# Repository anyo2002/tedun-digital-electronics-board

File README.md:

# TEDUN - Digital Electronics Development Board

## 📌 Overview
The **TEDUN (Tarjeta de Electrónica Digital de la UNAL)** is an academic project developed as part of an Embedded Systems course in Electronic Engineering.

> ⚠️ Note: The project name does not represent an official product of UNAL. It only reflects the academic context in which it was developed.

This project consists of the design and implementation of a **custom development board** based on:
- A **F133A RISC-V processor**
- A **Trion T8Q144C3 FPGA**

The board enables hardware experimentation with multiple modules (Bluetooth, audio, infrared, etc.) using communication protocols such as **UART, I2S, SPI**, and **GPIO**.

---

## 🎯 Objectives
- Design a complete embedded development board
- Enable communication between a processor and an FPGA
- Support hardware testing using multiple digital interfaces
- Develop schematics and PCB using KiCad
- Implement FPGA programming using open-source tools

---

## ⚙️ Key Features

- Powered via **Micro-USB (~5V)**
- Boot via **SD card with Tina Linux**
- UART communication with a computer (via USB-UART converter)
- FPGA programming using **OpenOCD (JTAG)**
- Communication between F133A and FPGA via **UART or SPI**
- 32 GPIO pins organized in **4 banks (3.3V + 5V output)**

---

## 🏗️ System Architecture

The system integrates:
- F133A processor (RISC-V)
- Trion T8 FPGA
- SD card storage
- Multiple communication interfaces

### Interfaces

#### 🔹 JTAG
Used to program the FPGA through OpenOCD running on the F133A.

#### 🔹 SD Card
Stores:
- Tina Linux OS
- Boot partitions
- Drivers and applications
- FPGA configuration files

#### 🔹 UART & I2S
- UART for communication with PC and FPGA
- I2S for audio/data transmission

#### 🔹 GPIO
- 32 configurable pins
- Used for hardware testing and module integration

---

## 🧩 Block Diagram

---

## 🔌 Interface Design

To validate the system, an **LctechPi board (F133A-based)** was used for testing.

Key points:
- Tina Linux was configured and deployed
- Required system packages were installed
- WiFi was tested but not included (cost optimization)

### Tool Selection

Two tools were evaluated:

#### ❌ openFPGALoader
- Supports Trion FPGA
- Limited to memory-based programming (Flash)
- ❌ Not suitable for JTAG-based programming via F133A

#### ✅ OpenOCD
- Open-source
- Supports JTAG
- Compatible with Trion FPGA
- ✔️ Selected solution

---

## 🧪 FPGA Programming with OpenOCD

OpenOCD was compiled for RISC-V and deployed on the board.

### Setup Steps:
1. Compile OpenOCD from source:
   https://github.com/riscv/riscv-openocd

2. Copy binary to:
/bin/

3. Copy scripts to:
/usr/local/share/openocd/scripts

4. Create configuration file:
openocd.cfg

### Example Configuration (JTAG via GPIO)

```bash
adapter driver sysfsgpio
transport select jtag
sysfsgpio jtag_nums 2 3 1 4

set CHIPNAME fpga_trion
source [find fpga/efinix_trion.cfg]

init
pld load fpga_trion.pld GPIO_demo.bit
```

## 🛠️ Hardware Design

The hardware design is based on:

- MangoPi (F133A reference)

- LctechPi board

- Trion T8 FPGA reference boards

## 🔋 Power Supply

- Input: Micro-USB (5V)
- Regulation using:
  - AMS1117 (instead of RY1303 from the MangoPi board)
  - Multiple LDO regulators

## Voltage Levels:
- 3.3V → I/O, GPIO, oscillator

- 1.8V → DRAM

- 2.8V → Communication block (PE)

- 1.2V → FPGA core

- 0.9V → Processor core

## ⚡ Power Sequencing

Implemented using:
- LM3880 power sequencer

Sequence: 
1. Enable FPGA + DRAM + PE
2. Enable processor core (0.9V)
3. Enable FPGA I/O

## 💾 SD Card
- Used for booting Tina Linux
- Based on MangoPi reference design

- Direct connection to F133A

## 🧠 F133A Connections

- JTAG → PG6–PG9
- UART0 → PE2 / PE3
- UART → PC6 / PC7
- SD → PF0–PF6
- SPI → PC2–PC7

## 🔲 FPGA (Trion T8)

- 13 banks available
- Selected banks: 1A, 3A, 3BC, 3D
- Supports:
  - JTAG programming
  - SPI & UART communication
  - GPIO expansion

## 🔌 GPIO

- 32 GPIO pins (4 banks × 8 pins)
- Each bank includes:
  - 3.3V output
  - GND
- Additional:
  - 5V output
  - UART interface
## ⏱️ Oscillators
- FPGA: 25 MHz oscillator

- Processor: MangoPi reference oscillator

## 🧾 PCB Design

Designed in KiCad:
- Compact layout
- Optimized routing
- 3D visualization available

## 📍 Pinout

- 32 GPIO pins available
- Organized in 4 banks
- Flexible usage:
  - GPIO
  - Communication interfaces
  - Special FPGA functions

## 📚 References
- F133A Datasheet
- Trion T8 Datasheet
- MangoPi Schematics

## 🧰 Tools & Technologies
- KiCad (PCB design)
- OpenOCD (FPGA programming)
- Tina Linux
- RISC-V architecture
- Embedded Linux

## 🚀 Skills Demonstrated
- Embedded Systems Design
- FPGA Integration
- Hardware Architecture
- PCB Design (KiCad)
- Power Electronics (LDO, sequencing)
- Communication Protocols (UART, SPI, I2S, JTAG)

## 👤 Authors

- Angel RUIZ
- Santiago DIAZ
- Daniel CELY

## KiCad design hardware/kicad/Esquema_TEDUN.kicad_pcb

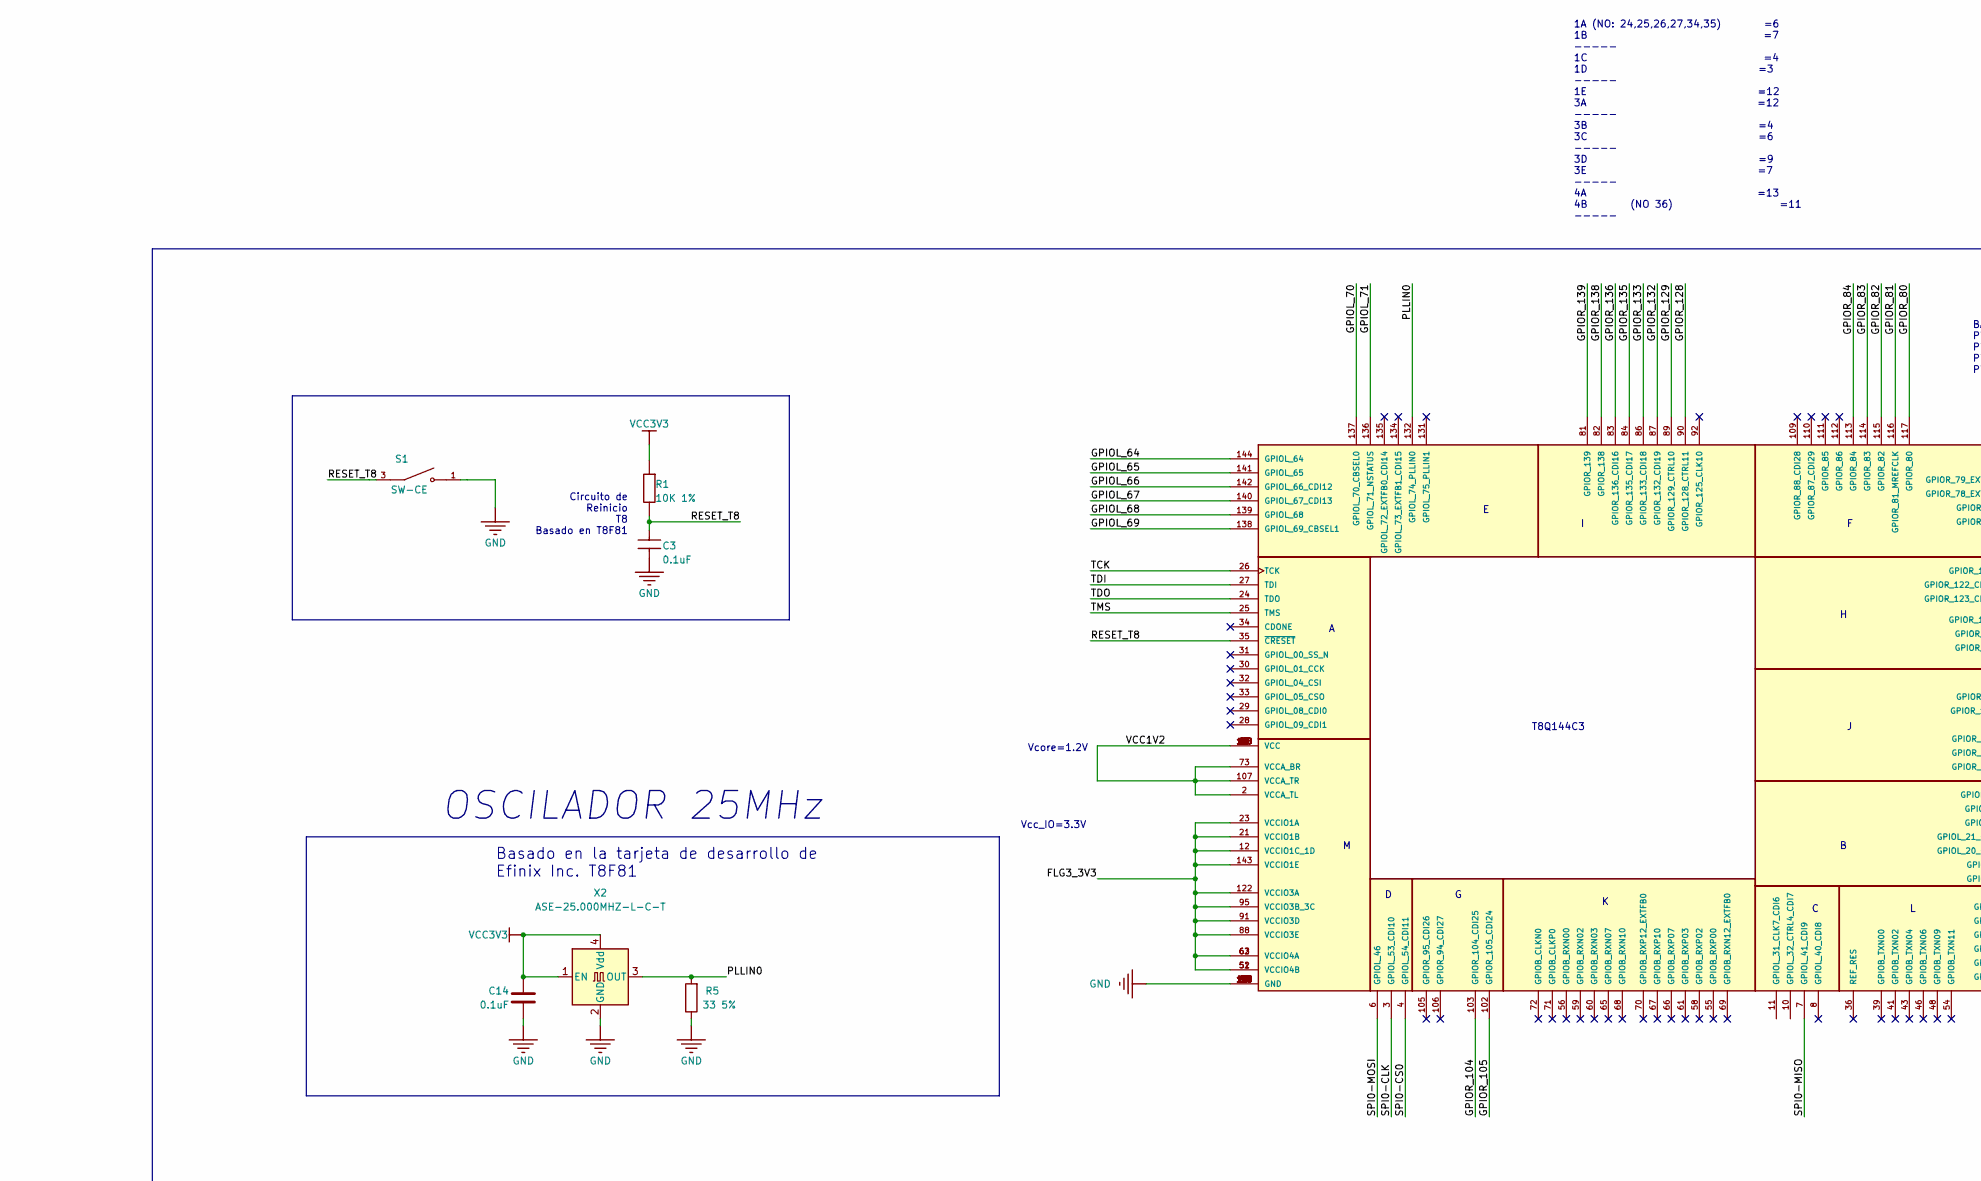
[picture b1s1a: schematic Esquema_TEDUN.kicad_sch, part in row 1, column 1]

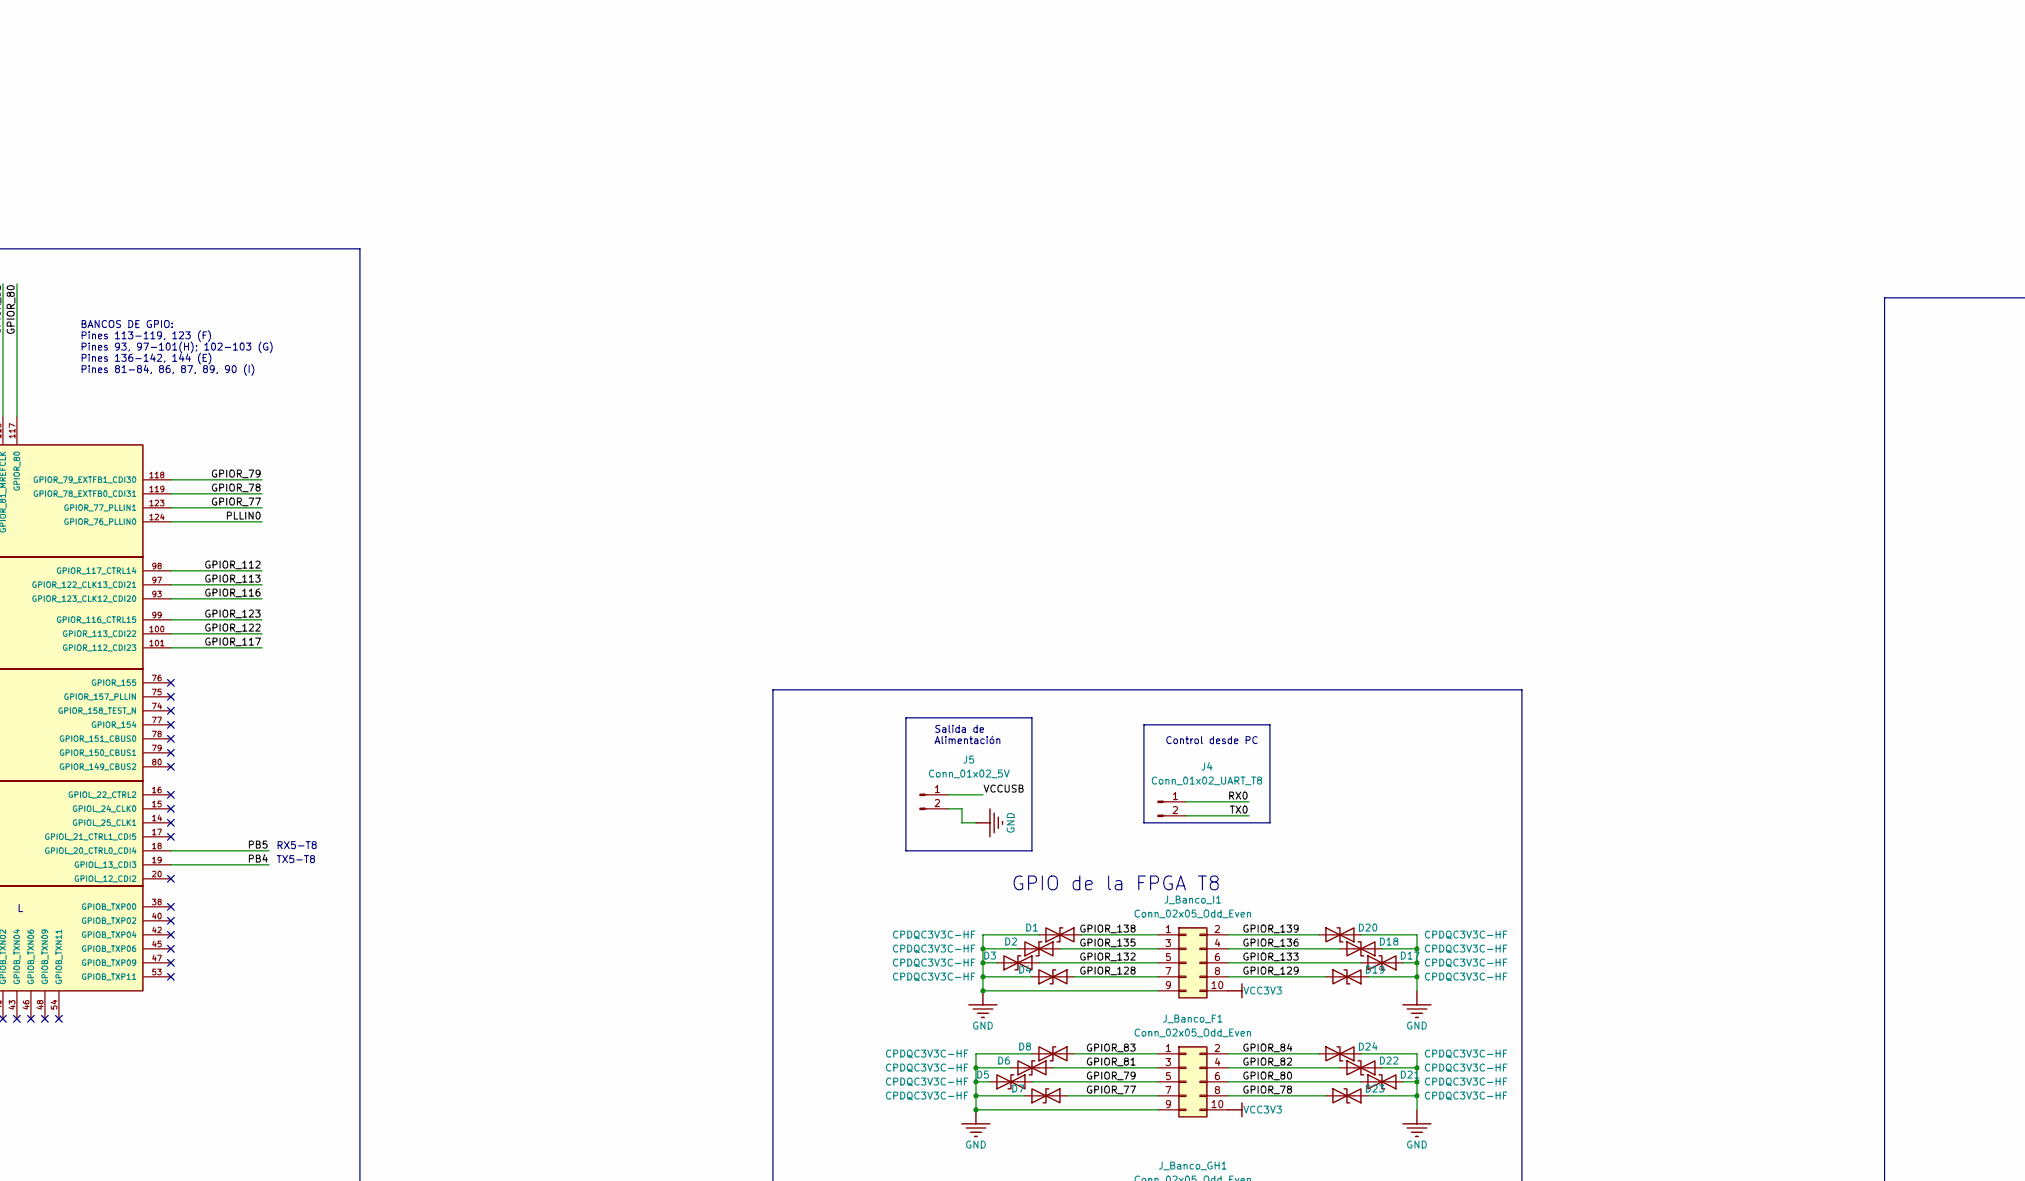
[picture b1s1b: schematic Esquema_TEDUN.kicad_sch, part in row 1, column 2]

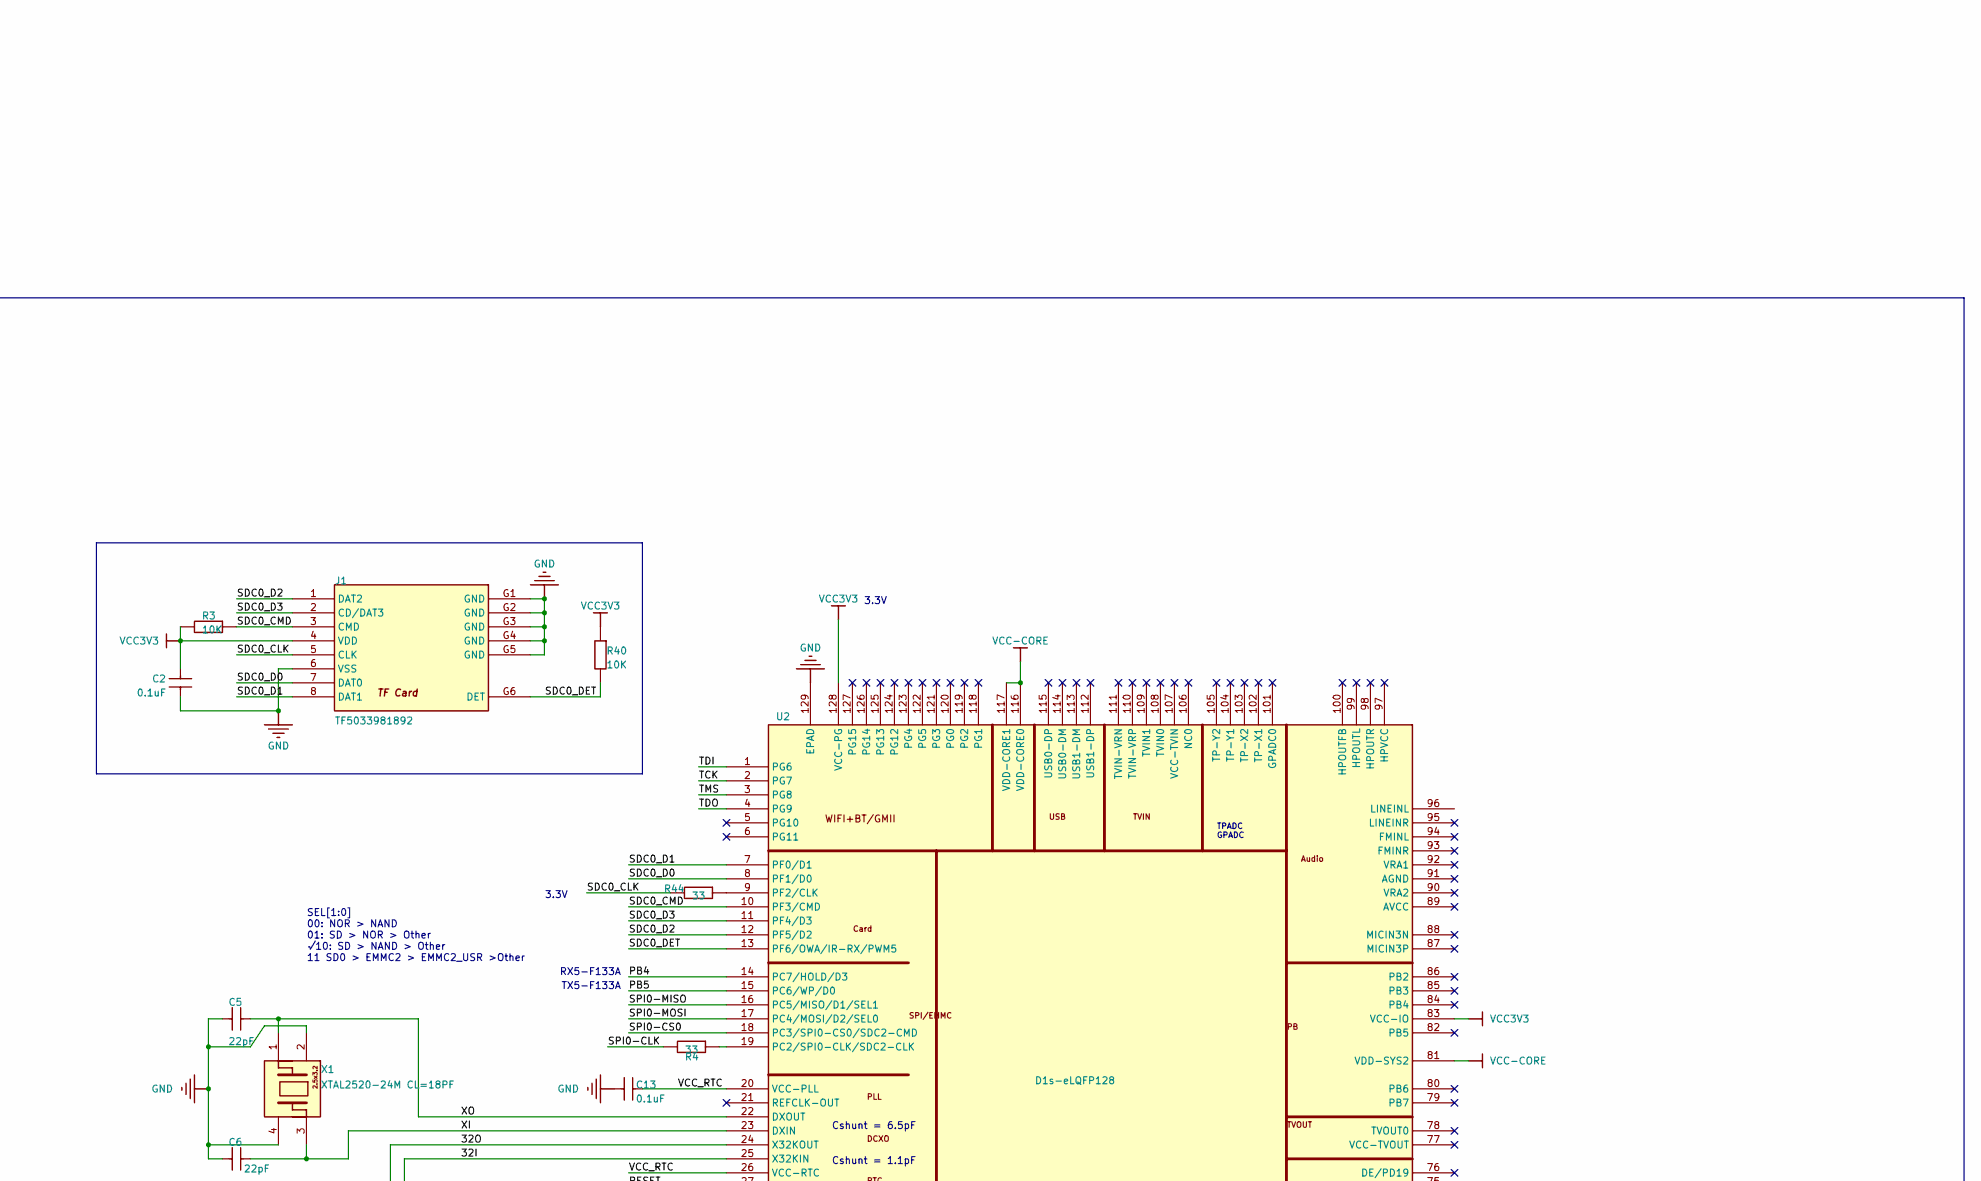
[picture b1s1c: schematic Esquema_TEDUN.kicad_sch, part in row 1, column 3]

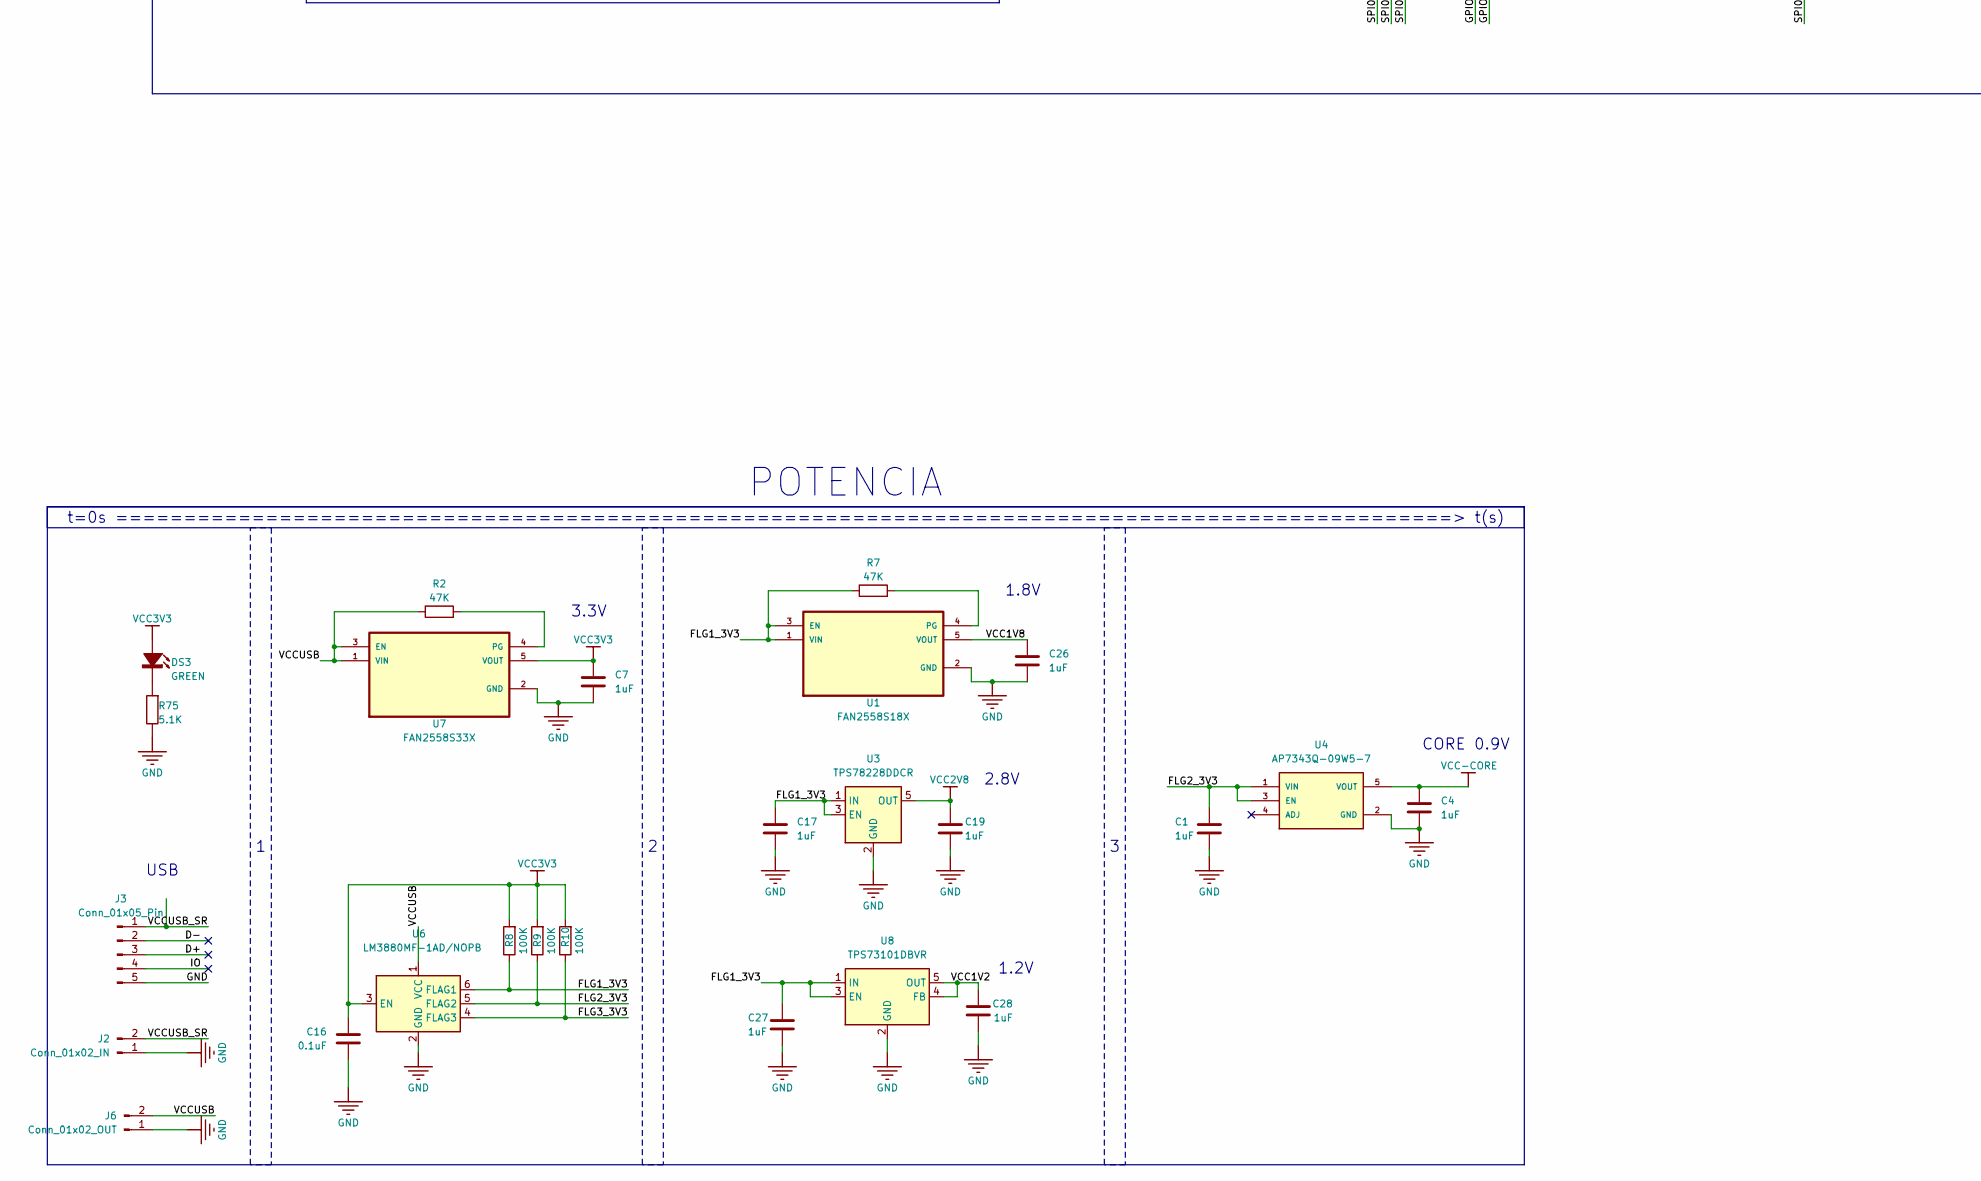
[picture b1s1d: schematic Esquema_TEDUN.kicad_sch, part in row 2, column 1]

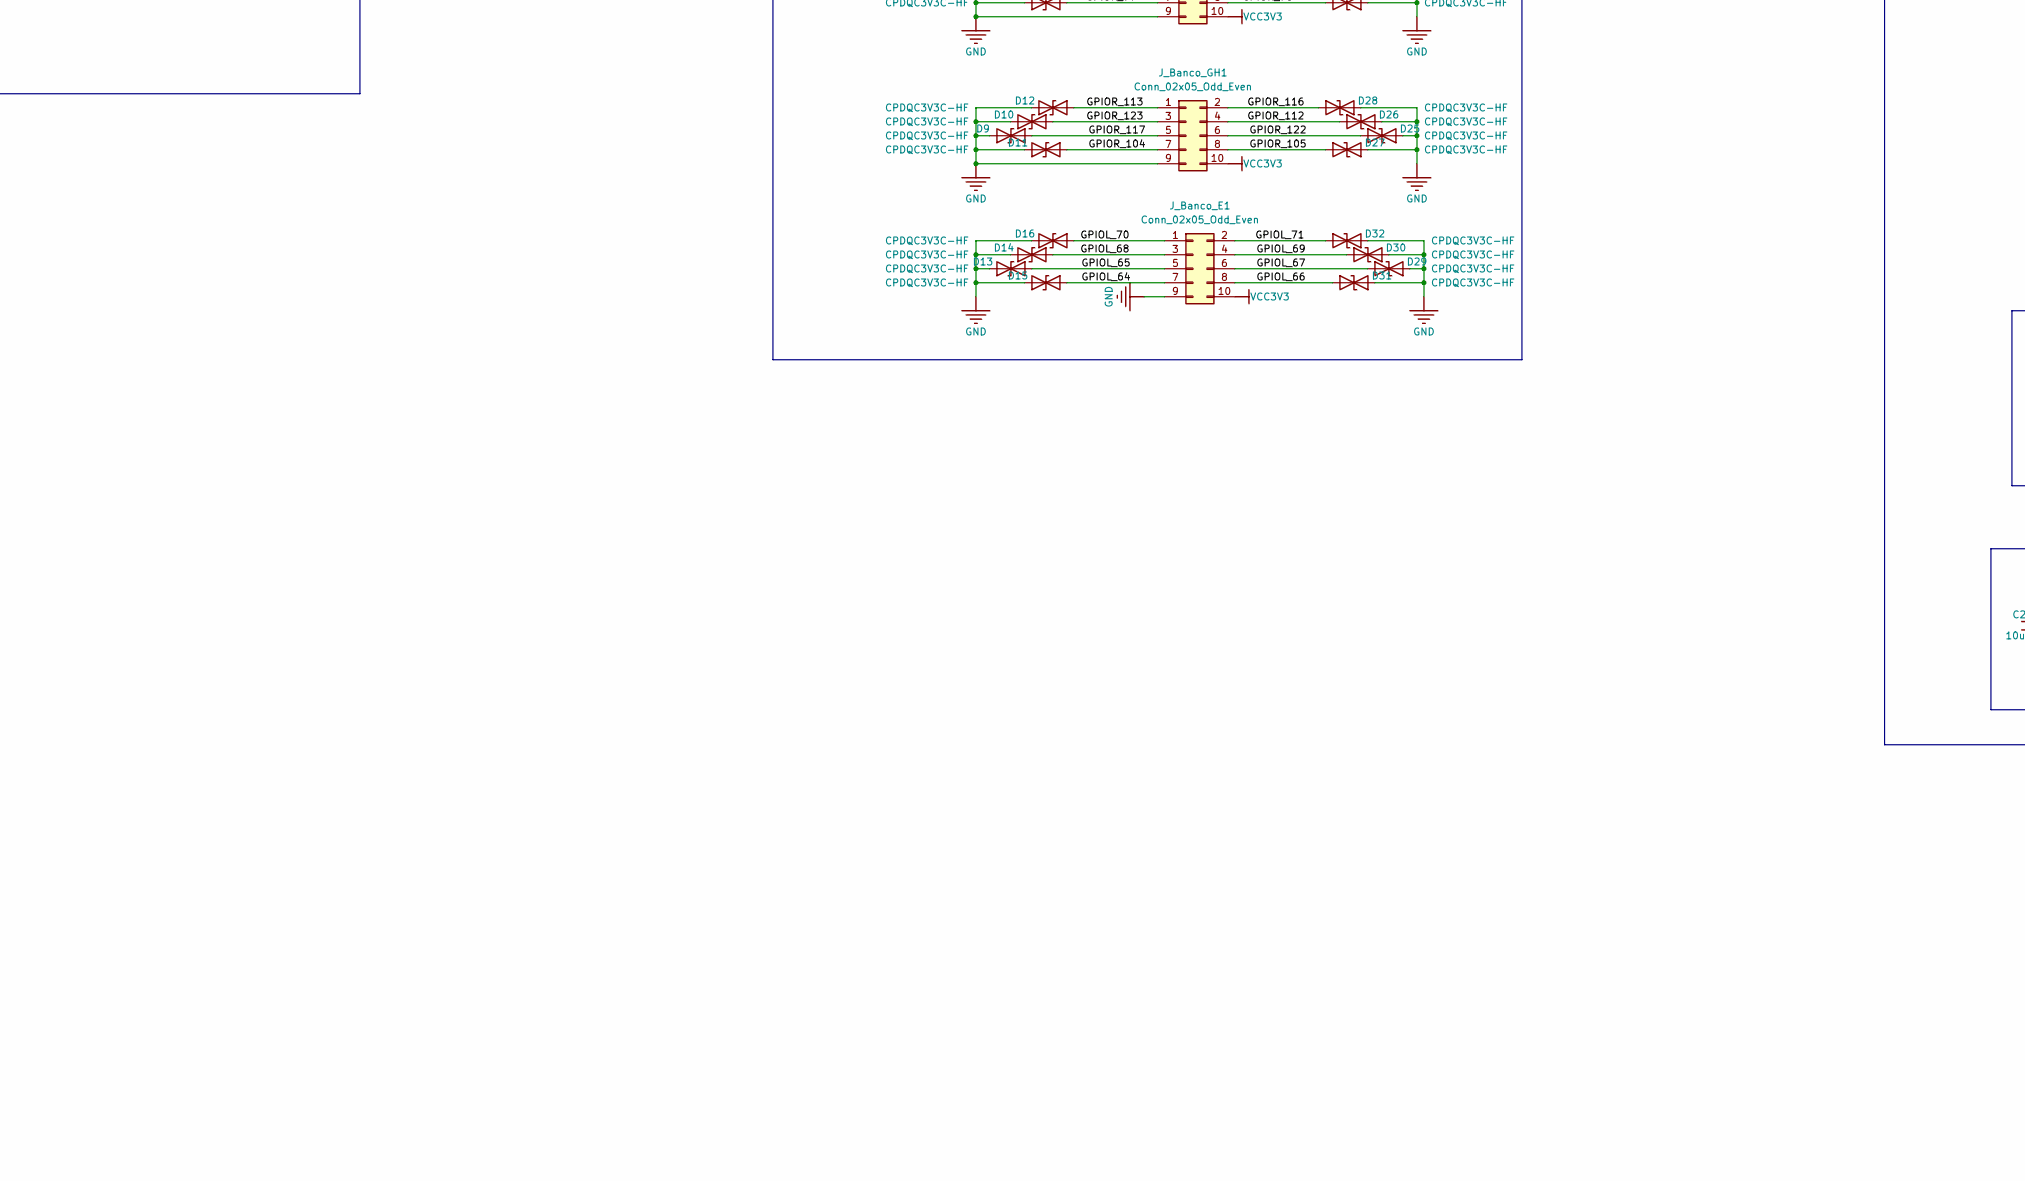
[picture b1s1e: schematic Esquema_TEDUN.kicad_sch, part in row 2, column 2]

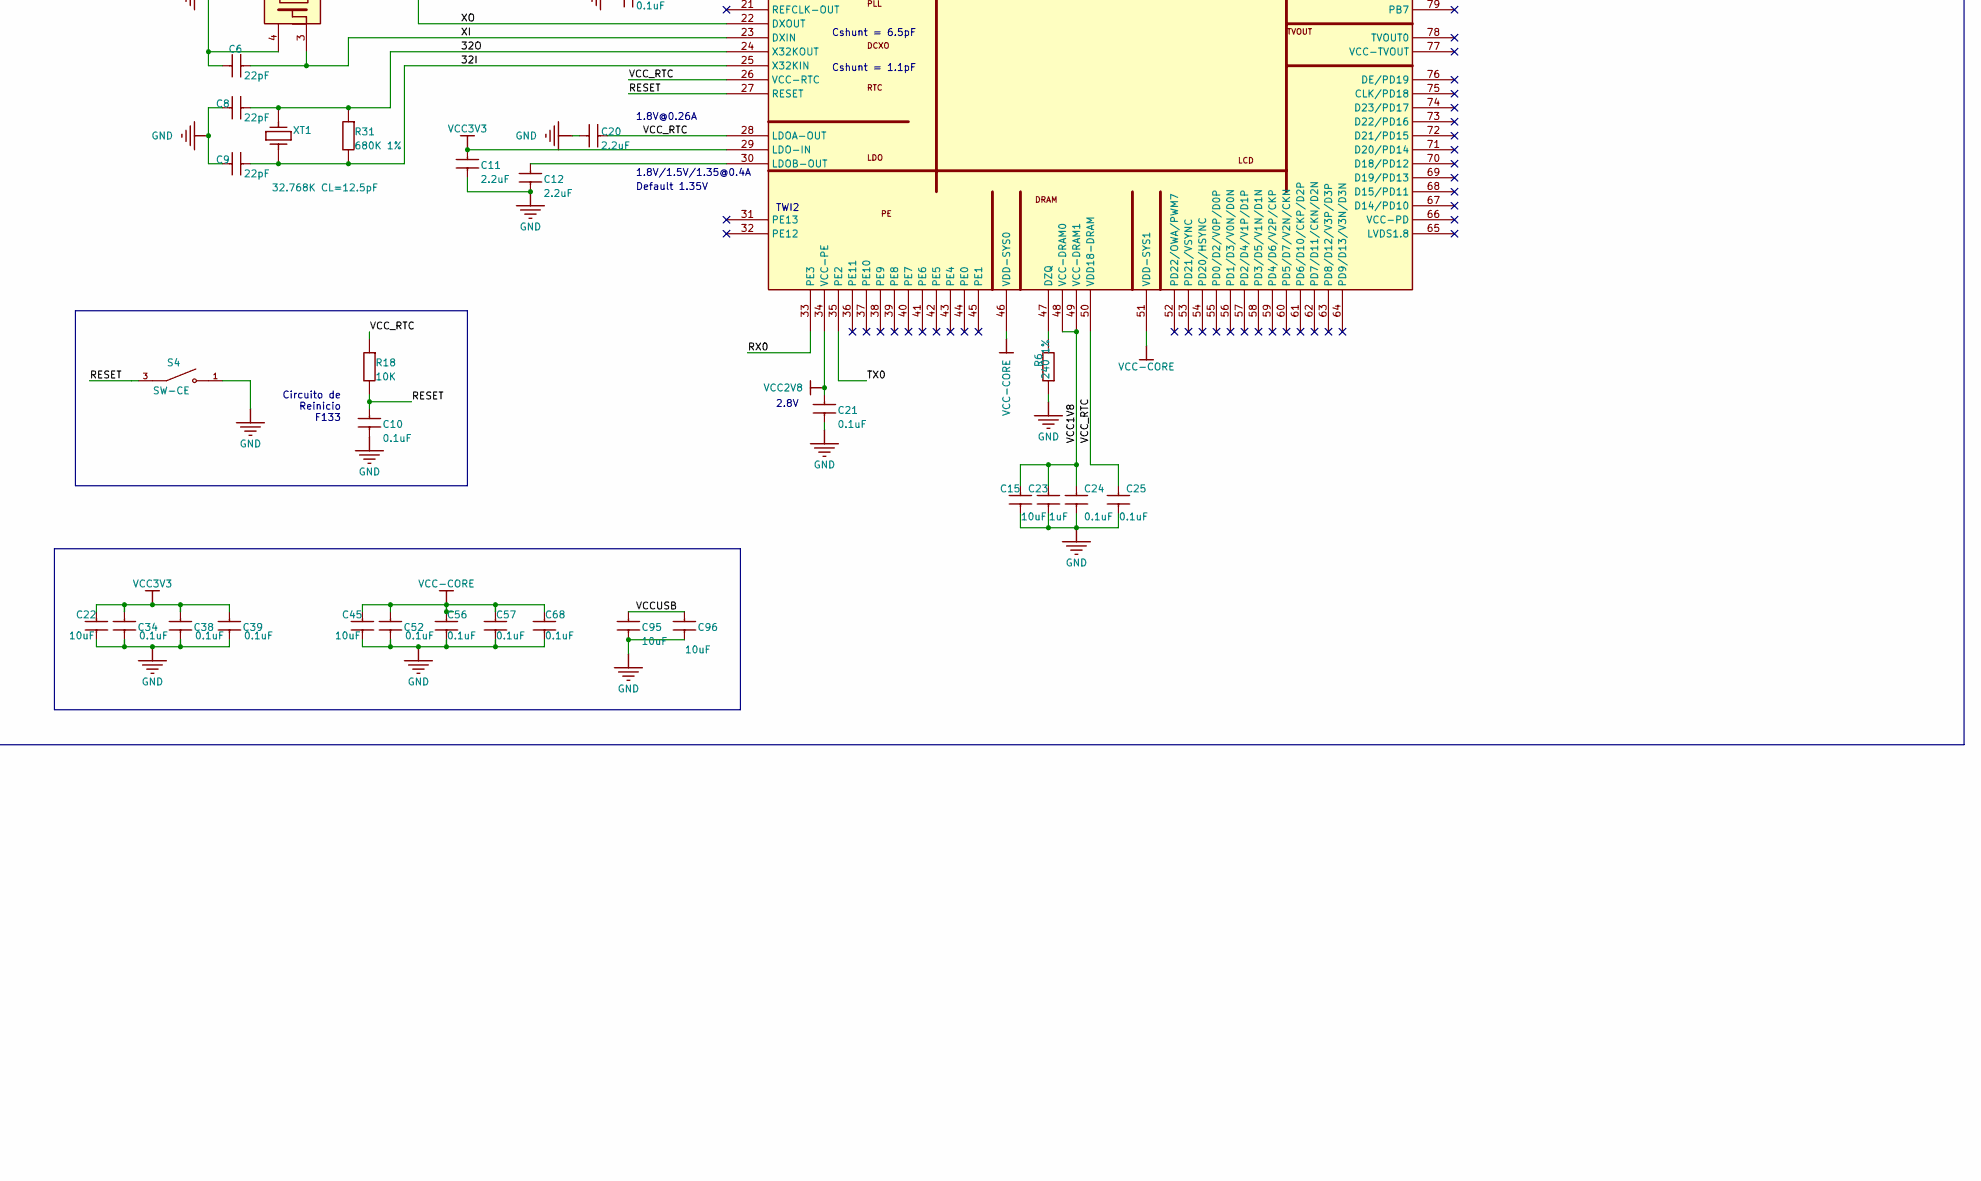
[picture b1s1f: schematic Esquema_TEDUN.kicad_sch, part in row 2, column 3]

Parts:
C1, C4, C7, C17, C19, C23, C26, C27, C28: 1uF; C_0402_1005Metric_Pad0.74x0.62mm_HandSolder
C2, C3, C10, C13, C14, C16, C21, C24, C25, C34, C38, C39, C52, C56, C57, C68: 0.1uF; C_0402_1005Metric_Pad0.74x0.62mm_HandSolder
C5, C6, C8, C9: 22pF; C_0402_1005Metric_Pad0.74x0.62mm_HandSolder
C11, C12, C20: 2.2uF; C_0402_1005Metric_Pad0.74x0.62mm_HandSolder
C15, C22, C45, C95, C96: 10uF; C_0402_1005Metric_Pad0.74x0.62mm_HandSolder
D1, D2, D3, D4, D5, D6, D7, D8, D9, D10, D11, D12, D13, D14, D15, D16, D17, D18, D19, D20, D21, D22, D23, D24, D25, D26, D27, D28, D29, D30, D31, D32: CPDQC3V3C-HF; DIODFN100X60X43-2N
DS3: GREEN; LED_0402_1005Metric_Pad0.77x0.64mm_HandSolder
J1: TF5033981892; TFCARD-1040310811
J2: Conn_01x02_IN; PinHeader_1x02_P2.54mm_Vertical
J3: Conn_01x05_Pin; PinHeader_1x05_P2.54mm_Vertical
J4: Conn_01x02_UART_T8; PinHeader_1x02_P2.54mm_Vertical
J5: Conn_01x02_5V; PinHeader_1x02_P2.54mm_Vertical
J6: Conn_01x02_OUT; PinHeader_1x02_P2.54mm_Vertical
J_Banco_E1: Conn_02x05_Odd_Even; PinHeader_2x05_P2.54mm_Vertical
J_Banco_F1: Conn_02x05_Odd_Even; PinHeader_2x05_P2.54mm_Vertical
J_Banco_GH1: Conn_02x05_Odd_Even; PinHeader_2x05_P2.54mm_Vertical
J_Banco_I1: Conn_02x05_Odd_Even; PinHeader_2x05_P2.54mm_Vertical
R1: 10K 1%; R_0402_1005Metric_Pad0.72x0.64mm_HandSolder
R2, R7: 47K; R_0402_1005Metric_Pad0.72x0.64mm_HandSolder
R3, R18, R40: 10K; R_0402_1005Metric_Pad0.72x0.64mm_HandSolder
R4, R44: 33; R_0402_1005Metric_Pad0.72x0.64mm_HandSolder
R5: 33 5%; R_0402_1005Metric_Pad0.72x0.64mm_HandSolder
R6: 240 1%; R_0402_1005Metric_Pad0.72x0.64mm_HandSolder
R8, R9, R10: 100K; R_0402_1005Metric_Pad0.72x0.64mm_HandSolder
R31: 680K 1%; R_0402_1005Metric_Pad0.72x0.64mm_HandSolder
R75: 5.1K; R_0402_1005Metric_Pad0.72x0.64mm_HandSolder
S1, S4: SW-CE; SW_PTS_647_SM38_SMTR2_LFS; PARTREV 11 Jun 19; DigiKey_Part_Number PTS647SM38SMTR2LFSTR-ND
U1: FAN2558S18X; FAN2558S33X
U2: D1s-eLQFP128; F133A_QFP129
U3: TPS78228DDCR; SOT-23-5
U4: AP7343Q-09W5-7; SOT-23-5
U5: T8Q144C3; QFP50P2200X2200X160-144N; PARTREV V3.6
U6: LM3880MF-1AD/NOPB; SOT-23-6
U7: FAN2558S33X
U8: TPS73101DBVR; SOT-23-5
X1: XTAL2520-24M CL=18PF; Oscillator_SMD_ECS_2520MV-xxx-xx-4Pin_2.5x2.0mm
X2: ASE-25.000MHZ-L-C-T; Oscillator_SMD_Abracon_ASE-4Pin_3.2x2.5mm
XT1: 32.768K CL=12.5pF; Y3215

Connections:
/32I: C9.1, R31.2, U2.25 (X32KIN), XT1.1
/32O: C8.1, R31.1, U2.24 (X32KOUT), XT1.2
/D+: J3.3
/D-: J3.2
/FLG1_3V3: C17.2, C27.1, R7.1, R8.1, U1.1 (VIN), U1.3 (EN), U3.1 (IN), U3.3 (EN), U6.6 (FLAG1), U8.1 (IN), U8.3 (EN)
/FLG2_3V3: C1.1, R9.1, U4.1 (VIN), U4.3 (EN), U6.5 (FLAG2)
/FLG3_3V3: R10.1, U5.12 (VCCIO1C_1D), U5.21 (VCCIO1B), U5.23 (VCCIO1A), U5.51 (VCCIO4B), U5.52 (VCCIO4B), U5.62 (VCCIO4A), U5.63 (VCCIO4A), U5.88 (VCCIO3E), U5.91 (VCCIO3D), U5.95 (VCCIO3B_3C), U5.122 (VCCIO3A), U5.143 (VCCIO1E), U6.4 (FLAG3)
/GPIOL_64: D15.2 (A2), J_Banco_E1.7, U5.144 (GPIOL_64)
/GPIOL_65: D13.2 (A2), J_Banco_E1.5, U5.141 (GPIOL_65)
/GPIOL_66: D31.2 (A2), J_Banco_E1.8, U5.142 (GPIOL_66_CDI12)
/GPIOL_67: D29.2 (A2), J_Banco_E1.6, U5.140 (GPIOL_67_CDI13)
/GPIOL_68: D14.2 (A2), J_Banco_E1.3, U5.139 (GPIOL_68)
/GPIOL_69: D30.2 (A2), J_Banco_E1.4, U5.138 (GPIOL_69_CBSEL1)
/GPIOL_70: D16.2 (A2), J_Banco_E1.1, U5.137 (GPIOL_70_CBSEL0)
/GPIOL_71: D32.2 (A2), J_Banco_E1.2, U5.136 (GPIOL_71_NSTATUS)
/GPIOR_77: D7.2 (A2), J_Banco_F1.7, U5.123 (GPIOR_77_PLLIN1)
/GPIOR_78: D23.2 (A2), J_Banco_F1.8, U5.119 (GPIOR_78_EXTFB0_CDI31)
/GPIOR_79: D5.2 (A2), J_Banco_F1.5, U5.118 (GPIOR_79_EXTFB1_CDI30)
/GPIOR_80: D21.2 (A2), J_Banco_F1.6, U5.117 (GPIOR_80)
/GPIOR_81: D6.2 (A2), J_Banco_F1.3, U5.116 (GPIOR_81_MREFCLK)
/GPIOR_82: D22.2 (A2), J_Banco_F1.4, U5.115 (GPIOR_82)
/GPIOR_83: D8.2 (A2), J_Banco_F1.1, U5.114 (GPIOR_83)
/GPIOR_84: D24.2 (A2), J_Banco_F1.2, U5.113 (GPIOR_84)
/GPIOR_104: D11.2 (A2), J_Banco_GH1.7, U5.103 (GPIOR_104_CDI25)
/GPIOR_105: D27.2 (A2), J_Banco_GH1.8, U5.102 (GPIOR_105_CDI24)
/GPIOR_112: D26.2 (A2), J_Banco_GH1.4, U5.98 (GPIOR_117_CTRL14)
/GPIOR_113: D12.2 (A2), J_Banco_GH1.1, U5.97 (GPIOR_122_CLK13_CDI21)
/GPIOR_116: D28.2 (A2), J_Banco_GH1.2, U5.93 (GPIOR_123_CLK12_CDI20)
/GPIOR_117: D9.2 (A2), J_Banco_GH1.5, U5.101 (GPIOR_112_CDI23)
/GPIOR_122: D25.2 (A2), J_Banco_GH1.6, U5.100 (GPIOR_113_CDI22)
/GPIOR_123: D10.2 (A2), J_Banco_GH1.3, U5.99 (GPIOR_116_CTRL15)
/GPIOR_128: D4.2 (A2), J_Banco_I1.7, U5.90 (GPIOR_128_CTRL11)
/GPIOR_129: D19.2 (A2), J_Banco_I1.8, U5.89 (GPIOR_129_CTRL10)
/GPIOR_132: D3.2 (A2), J_Banco_I1.5, U5.87 (GPIOR_132_CDI19)
/GPIOR_133: D17.2 (A2), J_Banco_I1.6, U5.86 (GPIOR_133_CDI18)
/GPIOR_135: D2.2 (A2), J_Banco_I1.3, U5.84 (GPIOR_135_CDI17)
/GPIOR_136: D18.2 (A2), J_Banco_I1.4, U5.83 (GPIOR_136_CDI16)
/GPIOR_138: D1.2 (A2), J_Banco_I1.1, U5.82 (GPIOR_138)
/GPIOR_139: D20.2 (A2), J_Banco_I1.2, U5.81 (GPIOR_139)
/IO: J3.4
/PB4: U2.14 (PC7/HOLD/D3), U5.19 (GPIOL_13_CDI3)
/PB5: U2.15 (PC6/WP/D0), U5.18 (GPIOL_20_CTRL0_CDI4)
/PLLIN0: R5.2, U5.124 (GPIOR_76_PLLIN0), U5.132 (GPIOL_74_PLLIN0), X2.3 (OUT)
/RESET: C10.1, R18.2, S4.3, U2.27 (RESET)
/RESET_T8: C3.1, R1.2, S1.3, U5.35 (~CRESET)
/RX0: J4.1, U2.33 (PE3)
/SDC0_CLK: J1.5 (CLK), R44.1
/SDC0_CMD: J1.3 (CMD), R3.2, U2.10 (PF3/CMD)
/SDC0_D0: J1.7 (DAT0), U2.8 (PF1/D0)
/SDC0_D1: J1.8 (DAT1), U2.7 (PF0/D1)
/SDC0_D2: J1.1 (DAT2), U2.12 (PF5/D2)
/SDC0_D3: J1.2 (CD/DAT3), U2.11 (PF4/D3)
/SDC0_DET: J1.G6 (DET), R40.1, U2.13 (PF6/OWA/IR-RX/PWM5)
/SPI0-CLK: R4.1, U5.3 (GPIOL_53_CDI10)
/SPI0-CS0: U2.18 (PC3/SPI0-CS0/SDC2-CMD), U5.4 (GPIOL_54_CDI11)
/SPI0-MISO: U2.16 (PC5/MISO/D1/SEL1), U5.7 (GPIOL_41_CDI9)
/SPI0-MOSI: U2.17 (PC4/MOSI/D2/SEL0), U5.6 (GPIOL_46)
/TCK: U2.2 (PG7), U5.26 (TCK)
/TDI: U2.1 (PG6), U5.27 (TDI)
/TDO: U2.4 (PG9), U5.24 (TDO)
/TMS: U2.3 (PG8), U5.25 (TMS)
/TX0: J4.2, U2.35 (PE2)
/VCC1V2: C28.2, U5.2 (VCCA_TL), U5.13 (VCC), U5.22 (VCC), U5.49 (VCC), U5.57 (VCC), U5.73 (VCCA_BR), U5.85 (VCC), U5.96 (VCC), U5.107 (VCCA_TR), U5.125 (VCC), U5.128 (VCC), U5.130 (VCC), U8.4 (FB), U8.5 (OUT)
/VCC1V8: C15.2, C23.2, C24.2, C26.1, U1.5 (VOUT), U2.48 (VCC-DRAM0), U2.49 (VCC-DRAM1)
/VCCUSB: C95.1, C96.1, J5.1, J6.2, R2.1, U6.1 (VCC), U7.1 (VIN), U7.3 (EN)
/VCCUSB_SR: J2.2, J3.1
/VCC_RTC: C13.1, C20.1, C25.2, R18.1, U2.20 (VCC-PLL), U2.26 (VCC-RTC), U2.28 (LDOA-OUT), U2.50 (VDD18-DRAM)
/XI: C6.1, U2.23 (DXIN), X1.3 (X2)
/XO: C5.1, U2.22 (DXOUT), X1.1 (X1)
AVDD2V8: C19.2, C21.2, U2.34 (VCC-PE), U3.5 (OUT)
GND: C1.2, C2.2, C3.2, C4.2, C5.2, C6.2, C7.2, C8.2, C9.2, C10.2, C11.2, C12.2, C13.2, C14.1, C15.1, C16.2, C17.1, C19.1, C20.2, C21.1, C22.1, C23.1, C24.1, C25.1, C26.2, C27.2, C28.1, C34.1, C38.1, C39.1, C45.1, C52.1, C56.1, C57.1, C68.1, C95.2, C96.2, D1.1 (A1), D2.1 (A1), D3.1 (A1), D4.1 (A1), D5.1 (A1), D6.1 (A1), D7.1 (A1), D8.1 (A1), D9.1 (A1), D10.1 (A1), D11.1 (A1), D12.1 (A1), D13.1 (A1), D14.1 (A1), D15.1 (A1), D16.1 (A1), D17.1 (A1), D18.1 (A1), D19.1 (A1), D20.1 (A1), D21.1 (A1), D22.1 (A1), D23.1 (A1), D24.1 (A1), D25.1 (A1), D26.1 (A1), D27.1 (A1), D28.1 (A1), D29.1 (A1), D30.1 (A1), D31.1 (A1), D32.1 (A1), J1.6 (VSS), J1.G1 (GND), J1.G2 (GND), J1.G3 (GND), J1.G4 (GND), J1.G5 (GND), J2.1, J3.5, J5.2, J6.1, J_Banco_E1.9, J_Banco_F1.9, J_Banco_GH1.9, J_Banco_I1.9, R5.1, R6.2, R75.2, S1.1, S4.1, U1.2 (GND), U2.129 (EPAD), U3.2 (GND), U3.4 (GND), U4.2 (GND), U5.1 (GND), U5.5 (GND), U5.9 (GND), U5.37 (GND), U5.44 (GND), U5.50 (GND), U5.64 (GND), U5.94 (GND), U5.104 (GND), U5.108 (GND), U5.120 (GND), U5.121 (GND), U5.126 (GND), U5.127 (GND), U5.129 (GND), U5.133 (GND), U6.2 (GND), U7.2 (GND), U8.2 (GND), X1.2 (NC1), X1.4 (NC2), X2.2 (GND)
unnamed: DS3.2, R75.1
unnamed: R7.2, U1.4 (PG)
unnamed: R6.1, U2.47 (DZQ)
unnamed: C12.1, U2.30 (LDOB-OUT)
unnamed: R4.2, U2.19 (PC2/SPI0-CLK/SDC2-CLK)
unnamed: R44.2, U2.9 (PF2/CLK)
unnamed: R2.2, U7.4 (PG)
VCC3V3: C2.1, C7.1, C11.1, C14.2, C16.1, C22.2, C34.2, C38.2, C39.2, DS3.1, J1.4 (VDD), J_Banco_E1.10, J_Banco_F1.10, J_Banco_GH1.10, J_Banco_I1.10, R1.1, R3.1, R8.2, R9.2, R10.2, R40.2, U2.29 (LDO-IN), U2.83 (VCC-IO), U2.128 (VCC-PG), U6.3 (EN), U7.5 (VOUT), X2.1 (EN), X2.4 (Vdd)
VCC-CORE: C4.1, C45.2, C52.2, C56.2, C57.2, C68.2, U2.46 (VDD-SYS0), U2.51 (VDD-SYS1), U2.81 (VDD-SYS2), U2.116 (VDD-CORE0), U2.117 (VDD-CORE1), U4.5 (VOUT)

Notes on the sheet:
t=0s ==================================================================================================> t(s)
OSCILADOR 25MHz
Vcc_IO=3.3V
1.8V/1.5V/1.35@0.4A
Circuito de Reinicio T8 Basado en T8F81
TWI2
Default 1.35V
3.3V
GPIO de la FPGA T8
T8Q144C3
Cshunt = 6.5pF
2.8V
RX5-T8
CORE 0.9V
SEL[1:0] 00: NOR > NAND 01: SD > NOR > Other √10: SD > NAND > Other 11 SD0 > EMMC2 > EMMC2_USR >Other
TPADC GPADC
USB
Basado en la tarjeta de desarrollo de Efinix Inc. T8F81
1.8V
TX5-T8
Cshunt = 1.1pF
1.2V
Vcore=1.2V
POTENCIA
Circuito de Reinicio F133
Salida de Alimentación
1.8V@0.26A
TX5-F133A
RX5-F133A
Control desde PC
1A (NO: 24,25,26,27,34,35) =6 1B =7 ----- 1C =4 1D =3 ----- 1E =12 3A =12 ----- 3B =4 3C =6 ----- 3D =9 3E =7 ----- 4A =13 4B (NO 36) =11 -----
BANCOS DE GPIO: Pines 113-119, 123 (F) Pines 93, 97-101(H); 102-103 (G) Pines 136-142, 144 (E) Pines 81-84, 86, 87, 89, 90 (I)

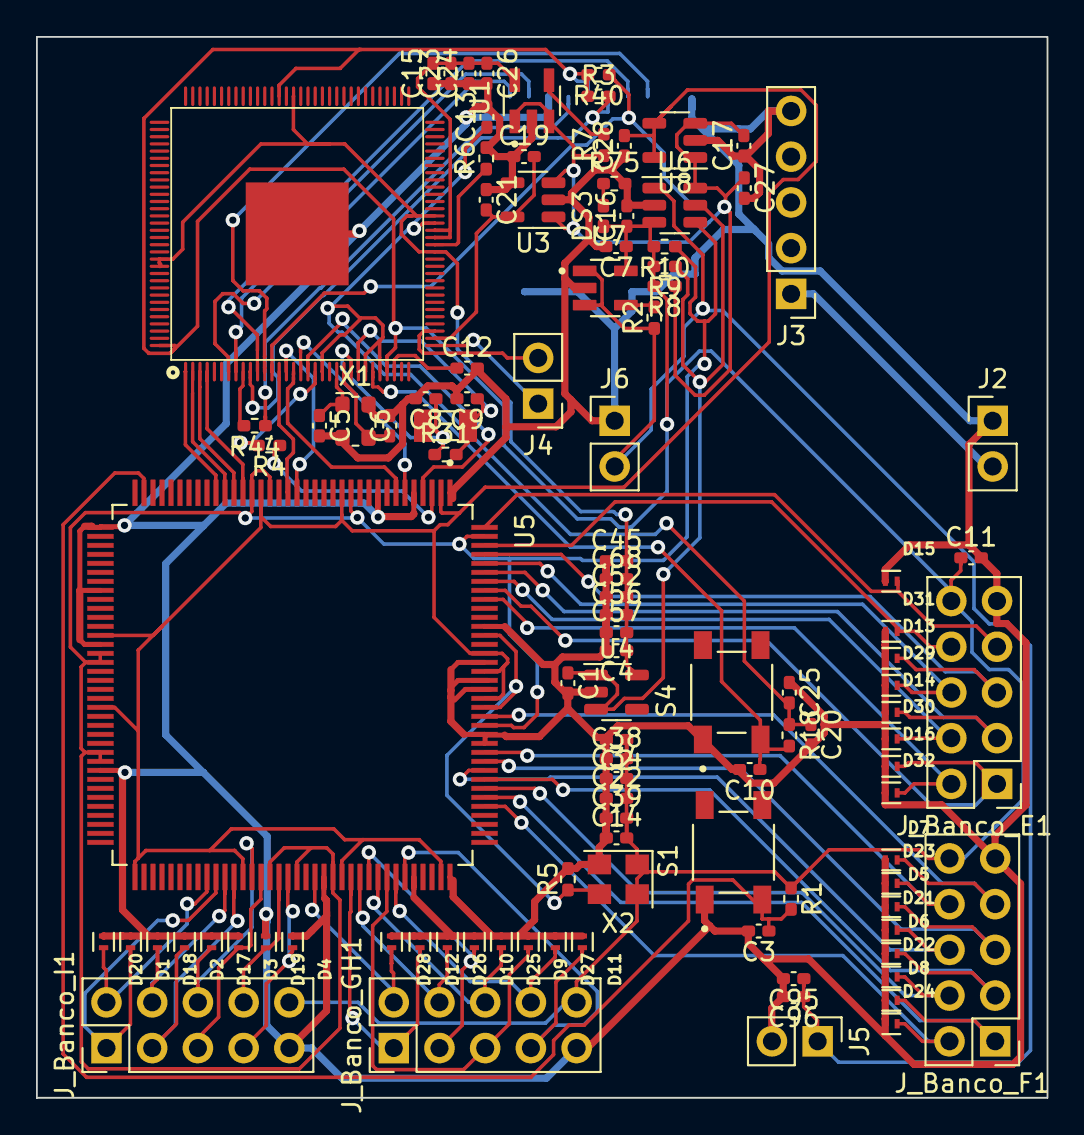
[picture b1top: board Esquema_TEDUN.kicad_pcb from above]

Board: 2 copper layers, 56.1 x 58.9 mm, 108 parts (1 on the bottom side), 77 nets.

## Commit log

2026-03-31 Initial commit - TEDUN project
2026-03-31 README images corrected
2026-03-31 README images referenced
2026-03-31 README image spacing
2026-03-31 Fix formatting of Authors section in README
2026-04-01 Add image to README
    Add an image to the README for visual enhancement.
